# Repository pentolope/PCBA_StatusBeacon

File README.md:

# Status Beacon Controller

A small USB-powered status beacon board: a microcontroller, one pushbutton, at least eight individually controllable RGB LEDs, and a small programming/debug connector.

`PCBA_StatusBeacon` is the benchmark's Status Beacon Controller: a small, USB-powered board carrying a microcontroller, one pushbutton, at least eight individually controllable RGB LEDs, and a small programming/debug connector. The brief fixes the function, the power source, the single pushbutton, a floor of at least eight individually controllable RGB LEDs, the exposure of a small programming/debug connector, and the qualitative goals of being inexpensive and easy to assemble; it also states a preference for a two-layer board unless there is a compelling reason not to. Everything else is deliberately unfixed — the brief explicitly hands the MCU, the LED technology, the exact board shape, and the connector family to the design agent, and it names no form for either connector. This is a detail-1 brief, so nearly all architecture, part selection, rail design, mechanical definition and stackup detail are left to the design agent, and this repository intentionally records those as open decisions rather than pre-answering them.

> **This board has not been designed.** There is no schematic, no layout and no
> part selection here — only the brief, a reading of the brief, and the
> scaffolding a design run needs. That is the intended state of this repository,
> not a gap in it.

## What the brief fixes, and what it leaves open

The brief pins down 13 requirements and deliberately leaves
16 decisions to whoever designs the board. The `Source` column says
which is which: `brief` is quoted from [BRIEF.md](BRIEF.md), `metadata` comes
from the benchmark catalogue, and `open` means the brief does not fix it.

| Aspect | Value | Source |
|---|---|---|
| Category | simple-digital | metadata |
| Difficulty | 1 of 5 | metadata |
| Brief detail | 1 of 5 (low-detail brief; most architecture left open) | metadata |
| Likely layer count | 2 | metadata |
| Primary stressors | basic component selection, simple placement/routing, LED current limiting, connector access | metadata |
| Function and power source | A small USB-powered status beacon board | brief |
| Controller | A microcontroller (specific device not named by the brief) | brief |
| User input | One pushbutton | brief |
| Indicators | At least eight individually controllable RGB LEDs (a floor, with no upper bound stated) | brief |
| Programming/debug access | A small programming/debug connector must be exposed; the brief names no family, form or pinout | brief |
| Cost and assembly posture | Inexpensive and easy to assemble | brief |
| Layer count preference | Two layers preferred, deviation allowed only with a compelling reason | brief |
| MCU, LED technology, board shape, connector family | Explicitly delegated to the design agent by the brief | brief |
| Status of stated requirements | Stated requirements are authoritative; open choices are to be decided and documented, not invented into requirements | brief |
| Rails, regulation, and power budget | Not fixed by the brief — design agent's choice | open |

The full split, with the verbatim brief text substantiating every fixed
requirement, is in [board/requirements.md](board/requirements.md) and
machine-readably in [board/requirements.json](board/requirements.json).

**Missing details are design freedom, not permission to fabricate unstated user
requirements.** A choice the brief left open is recorded as a decision, with its
reasoning — never promoted into a requirement.

## Benchmark position

| | |
|---|---|
| Benchmark id | 1 of 32 |
| Category | simple-digital |
| Difficulty | 1 / 5 |
| Brief detail | 1 / 5 |
| Likely layer count | 2 |
| Primary stressors | basic component selection, simple placement/routing, LED current limiting, connector access |

At difficulty 1/5 and detail 1/5 in the `simple-digital` category, this board tests whether a design agent can execute competently with almost no specification handed to it — the metadata's stressors are basic component selection, simple placement/routing, LED current limiting, and connector access. The interesting question is not whether the circuit is hard, but whether the agent makes and justifies its own choices (MCU, LED technology, shape, connector family) instead of fabricating requirements the brief never stated. Two of those stressors — LED current limiting and connector access — are where the missing detail bites hardest: with no brightness, current, environment or mechanical context stated, the per-LED current, the total the board draws from USB with the whole array lit, and the physical usability of the connectors all have to be derived and shown rather than asserted.

This repository is one of thirty-two. The suite, the protocol and the results
live in [PCBA_AutoDesignAndTest_Bench](https://github.com/pentolope/PCBA_AutoDesignAndTest_Bench).

## Repository layout

| Path | Contents |
|---|---|
| `BRIEF.md` | the supplied brief — authoritative, preserved byte for byte, never edited |
| `board/requirements.md` | what the brief fixes, what it leaves open, and where decisions get recorded |
| `board/requirements.json` | the same split, machine-readable, each fixed requirement bound to brief text |
| `board/manifest.template.json` | the toolkit's minimum manifest, pre-filled for this board |
| `board/toolchain.json` | where this board's build finds KiCad and the router |
| `benchmark/metadata.json` | the supplied catalogue entry — category, difficulty, detail, stressors |
| `docs/architecture.md` | the decisions this board must make, as questions, unanswered |
| `docs/sources.md` | the classes of evidence the design will have to cite |
| `docs/status.md` | what exists, what does not, and what is deliberately absent |
| `candidates/` | disposable search output, ignored by Git |
| `.claude/skills/` | the accountability-review skill [CLAUDE.md](CLAUDE.md) requires before a push |
| `tooling/PCBA_AutoDesignAndTest` | the shared verification/routing/release toolkit, as a pinned submodule |

## Getting the repository

The toolkit is a submodule and carries KiCad Routing Tools as a submodule of its
own, so clone recursively:

```bash
git clone --recursive https://github.com/pentolope/PCBA_StatusBeacon.git
```

```bash
git submodule update --init --recursive
```

## Designing the board

Generic verification, routing and release logic is **not** written here. It is
consumed from `tooling/PCBA_AutoDesignAndTest`, which is board-agnostic by
construction and must stay that way; this repository owns the board and nothing
else. Start from
[the toolkit's onboarding guide](tooling/PCBA_AutoDesignAndTest/examples/onboarding.md),
and see [CLAUDE.md](CLAUDE.md) for the rules a design run works under.

```bash
python3 tooling/PCBA_AutoDesignAndTest/run.py preflight
```

## Brief integrity

`BRIEF.md` SHA-256 `57889bbb86eda40bff9fa7fda22a93a18370e8318bfdb673a84f301cc4c06788`

Every quotation in `board/requirements.json` is bound to those exact bytes. If
the brief ever changes, the bindings are stale by construction — which is the
point of recording the digest.

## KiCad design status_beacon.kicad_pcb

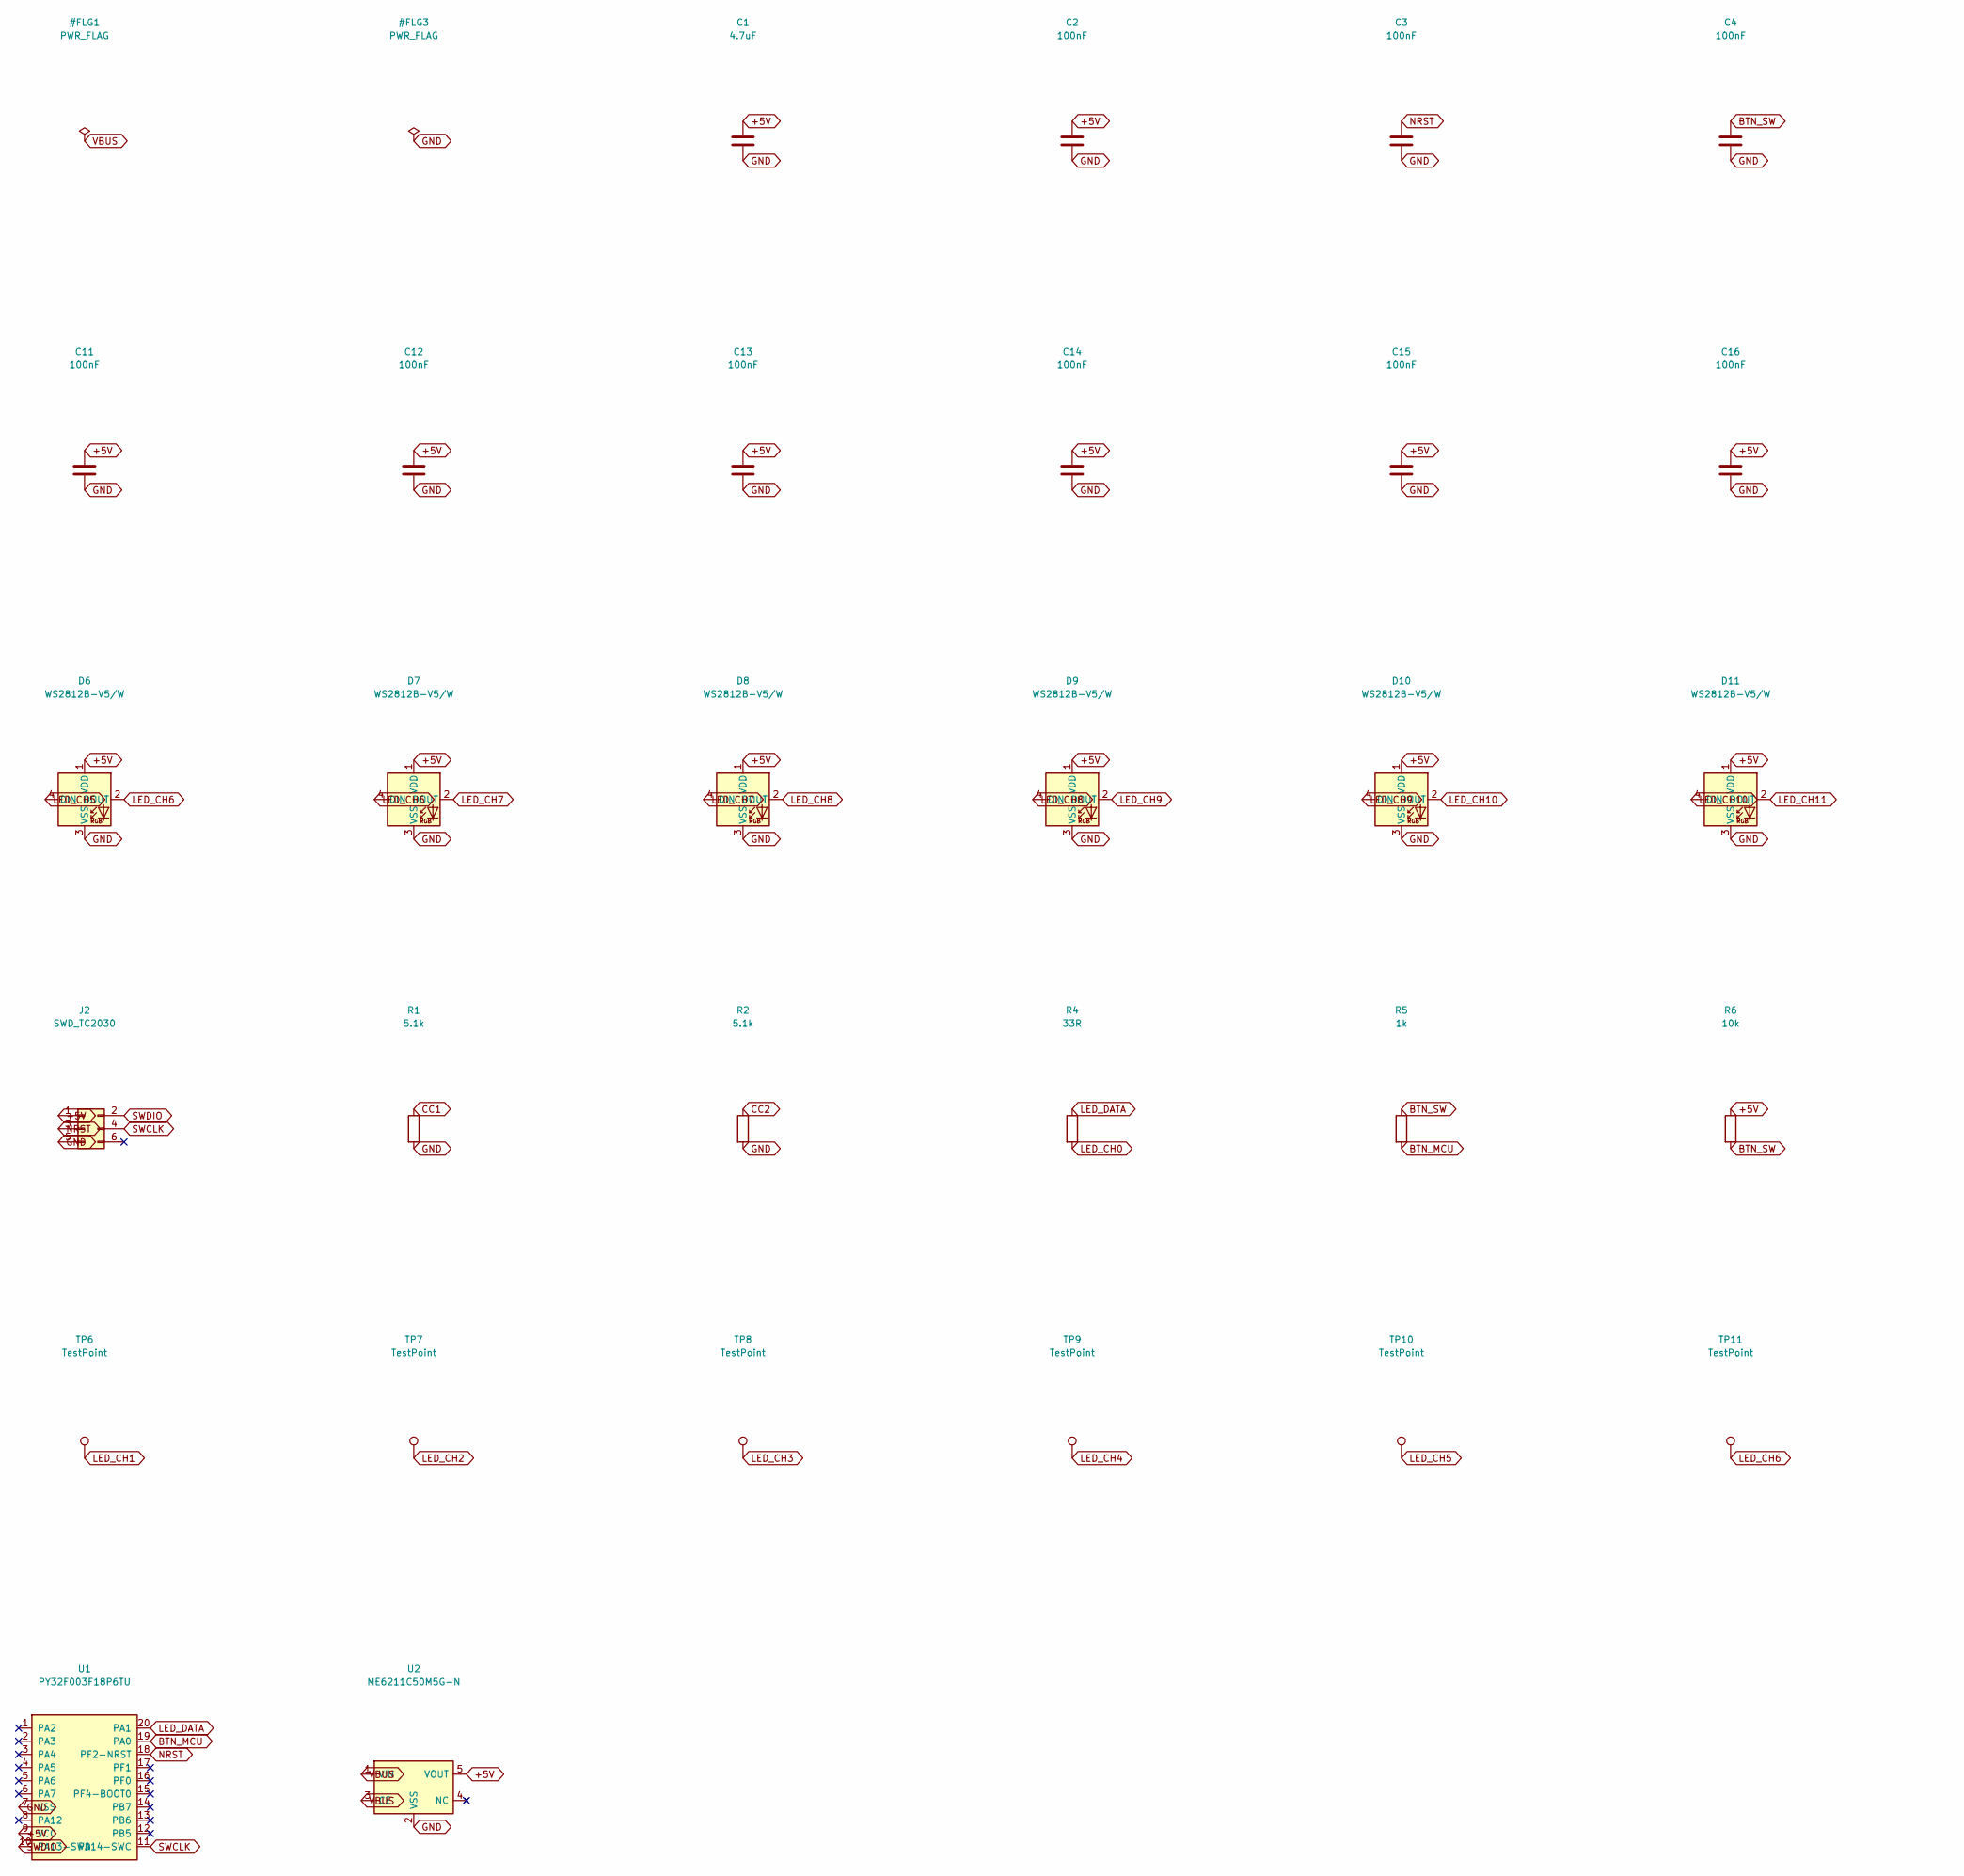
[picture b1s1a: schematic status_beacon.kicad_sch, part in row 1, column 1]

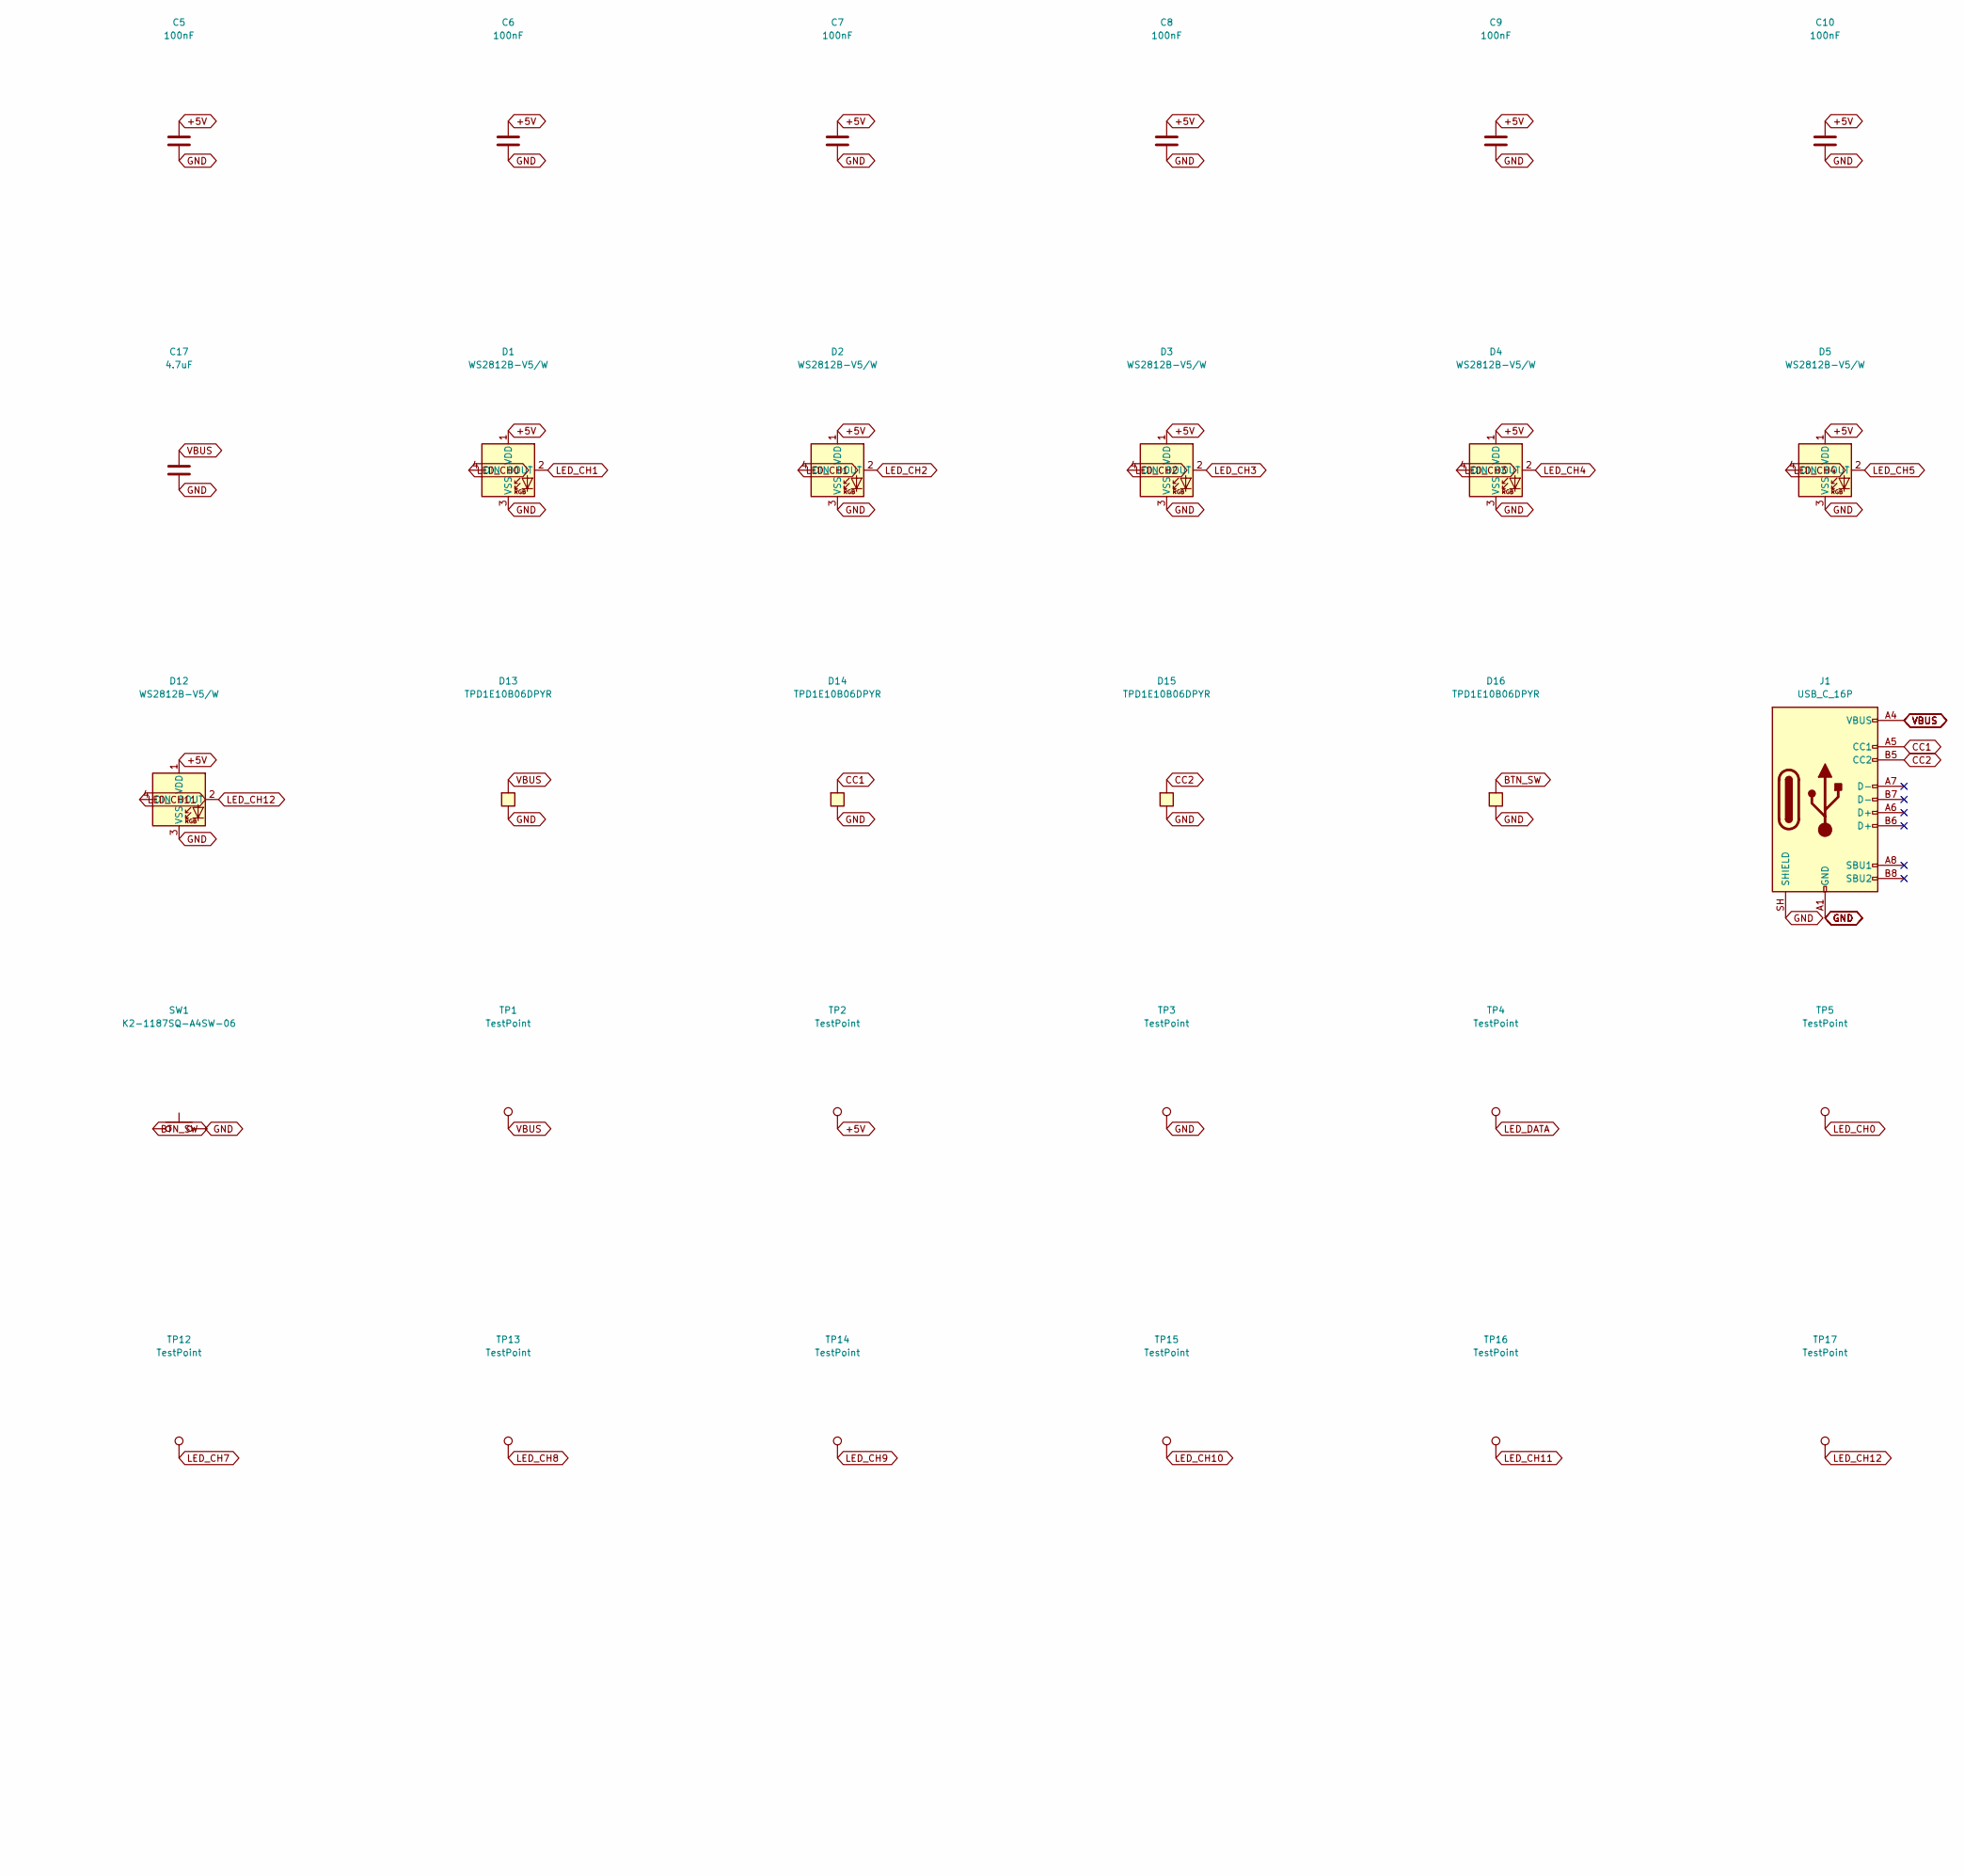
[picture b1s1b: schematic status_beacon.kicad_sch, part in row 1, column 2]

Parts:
C1, C17: 4.7uF; C_0805_2012Metric; LCSC C1779
C2, C3, C4, C5, C6, C7, C8, C9, C10, C11, C12, C13, C14, C15, C16: 100nF; C_0402_1005Metric; LCSC C1525
D1, D2, D3, D4, D5, D6, D7, D8, D9, D10, D11, D12: WS2812B-V5/W; LED_WS2812B_PLCC4_5.0x5.0mm_P3.2mm; MPN WS2812B-V5/W; LCSC C2874885
D13, D14, D15, D16: TPD1E10B06DPYR; TI_X1SON-2_1.0x0.6mm_P0.65mm; MPN TPD1E10B06DPYR; LCSC C48260
J1: USB_C_16P; USB_C_Receptacle_HRO_TYPE-C-31-M-12_LCSC; MPN TYPE-C-31-M-12; LCSC C165948
J2: SWD_TC2030; Tag-Connect_TC2030-IDC-NL_2x03_P1.27mm_Vertical
R1, R2: 5.1k; R_0402_1005Metric; LCSC C25905
R4: 33R; R_0402_1005Metric; LCSC C25105
R5: 1k; R_0402_1005Metric; LCSC C11702
R6: 10k; R_0402_1005Metric; LCSC C25744
SW1: K2-1187SQ-A4SW-06; SW_SPST_SKQG_WithoutStem; MPN K2-1187SQ-A4SW-06; LCSC C92584
TP1, TP2, TP3, TP4, TP5, TP6, TP7, TP8, TP9, TP10, TP11, TP12, TP13, TP14, TP15, TP16, TP17: TestPoint; TestPoint_Pad_D1.0mm
U1: PY32F003F18P6TU; TSSOP-20_4.4x6.5mm_P0.65mm; MPN PY32F003F18P6TU; LCSC C5379864
U2: ME6211C50M5G-N; SOT-23-5; MPN ME6211C50M5G-N; LCSC C236670

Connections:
+5V: C1.1, C2.1, C5.1, C6.1, C7.1, C8.1, C9.1, C10.1, C11.1, C12.1, C13.1, C14.1, C15.1, C16.1, D1.1 (VDD), D2.1 (VDD), D3.1 (VDD), D4.1 (VDD), D5.1 (VDD), D6.1 (VDD), D7.1 (VDD), D8.1 (VDD), D9.1 (VDD), D10.1 (VDD), D11.1 (VDD), D12.1 (VDD), J2.1, R6.1, TP2.1, U1.9 (VCC), U2.5 (VOUT)
BTN_MCU: R5.2, U1.19 (PA0)
BTN_SW: C4.1, D16.2 (A2), R5.1, R6.2, SW1.1
CC1: D14.2 (A2), J1.A5 (CC1), R1.1
CC2: D15.2 (A2), J1.B5 (CC2), R2.1
GND: C1.2, C2.2, C3.2, C4.2, C5.2, C6.2, C7.2, C8.2, C9.2, C10.2, C11.2, C12.2, C13.2, C14.2, C15.2, C16.2, C17.2, D1.3 (VSS), D2.3 (VSS), D3.3 (VSS), D4.3 (VSS), D5.3 (VSS), D6.3 (VSS), D7.3 (VSS), D8.3 (VSS), D9.3 (VSS), D10.3 (VSS), D11.3 (VSS), D12.3 (VSS), D13.1 (A1), D14.1 (A1), D15.1 (A1), D16.1 (A1), J1.A1 (GND), J1.A12 (GND), J1.B1 (GND), J1.B12 (GND), J1.SH (SHIELD), J2.5, R1.2, R2.2, SW1.2, TP3.1, U1.7 (VSS), U2.2 (VSS)
LED_CH0: D1.4 (DIN), R4.2, TP5.1
LED_CH1: D1.2 (DOUT), D2.4 (DIN), TP6.1
LED_CH2: D2.2 (DOUT), D3.4 (DIN), TP7.1
LED_CH3: D3.2 (DOUT), D4.4 (DIN), TP8.1
LED_CH4: D4.2 (DOUT), D5.4 (DIN), TP9.1
LED_CH5: D5.2 (DOUT), D6.4 (DIN), TP10.1
LED_CH6: D6.2 (DOUT), D7.4 (DIN), TP11.1
LED_CH7: D7.2 (DOUT), D8.4 (DIN), TP12.1
LED_CH8: D8.2 (DOUT), D9.4 (DIN), TP13.1
LED_CH9: D9.2 (DOUT), D10.4 (DIN), TP14.1
LED_CH10: D10.2 (DOUT), D11.4 (DIN), TP15.1
LED_CH11: D11.2 (DOUT), D12.4 (DIN), TP16.1
LED_CH12: D12.2 (DOUT), TP17.1
LED_DATA: R4.1, TP4.1, U1.20 (PA1)
NRST: C3.1, J2.3, U1.18 (PF2-NRST)
SWCLK: J2.4, U1.11 (PA14-SWC)
SWDIO: J2.2, U1.10 (PA13-SWD)
VBUS: C17.1, D13.2 (A2), J1.A4 (VBUS), J1.A9 (VBUS), J1.B4 (VBUS), J1.B9 (VBUS), TP1.1, U2.1 (VIN), U2.3 (CE)

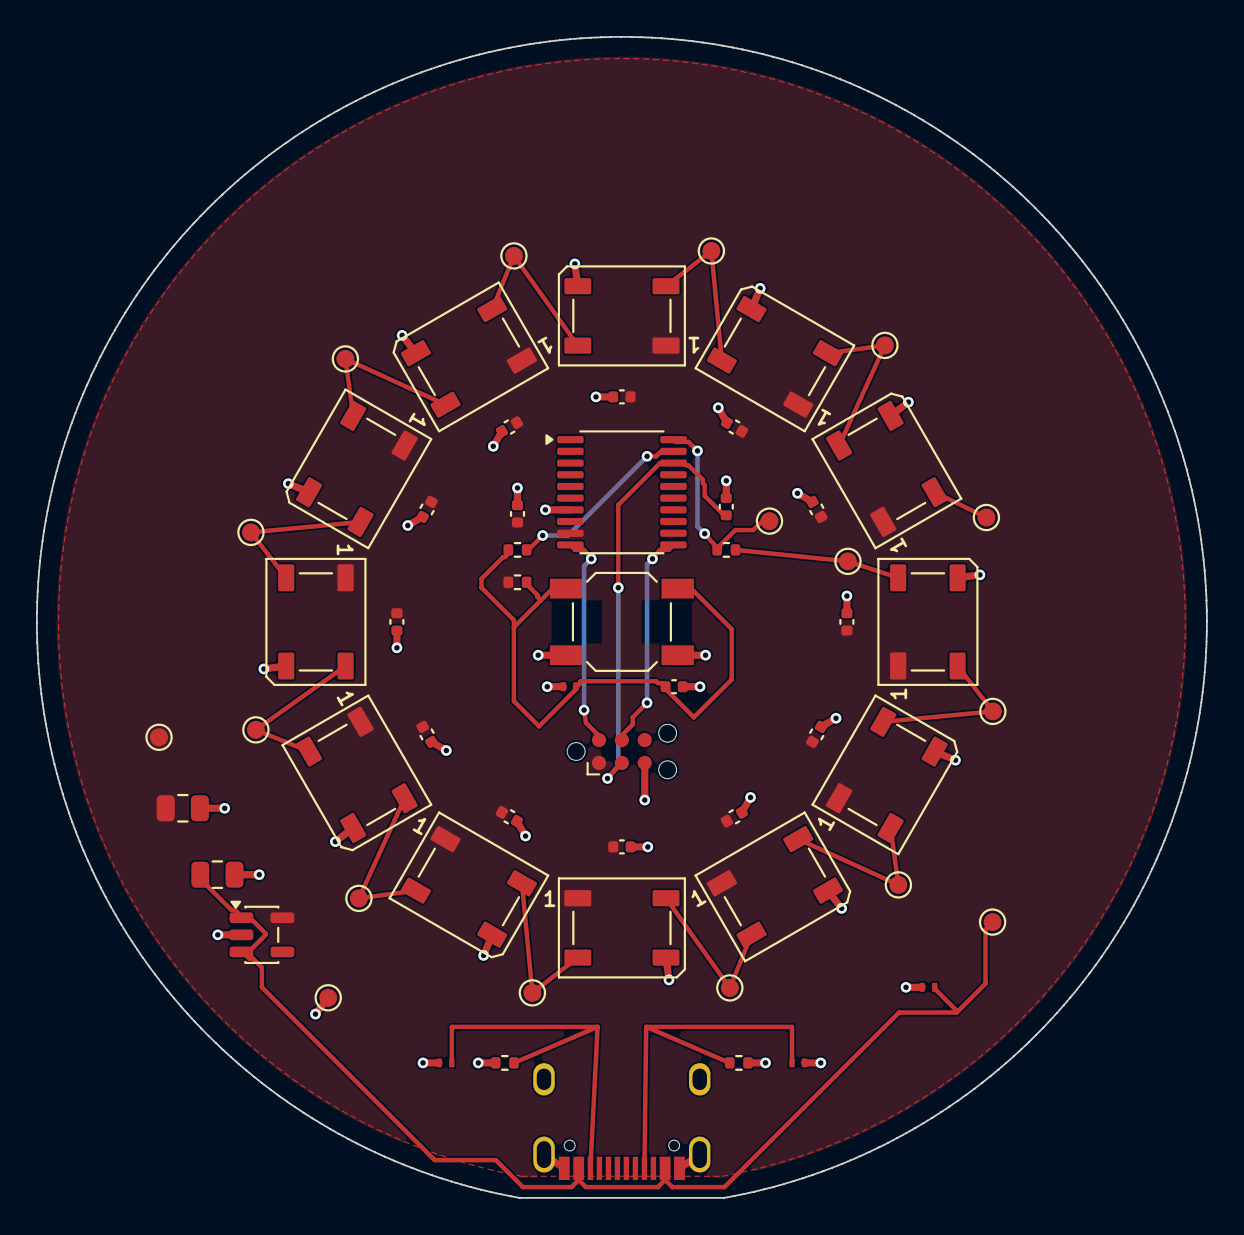
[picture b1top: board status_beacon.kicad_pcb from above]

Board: 2 copper layers, 65.0 x 64.5 mm, 60 parts (0 on the bottom side), 24 nets.
